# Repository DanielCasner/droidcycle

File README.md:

droidcycle
==========

Hardware and firmware for my Android phone based electric bicycle computer.

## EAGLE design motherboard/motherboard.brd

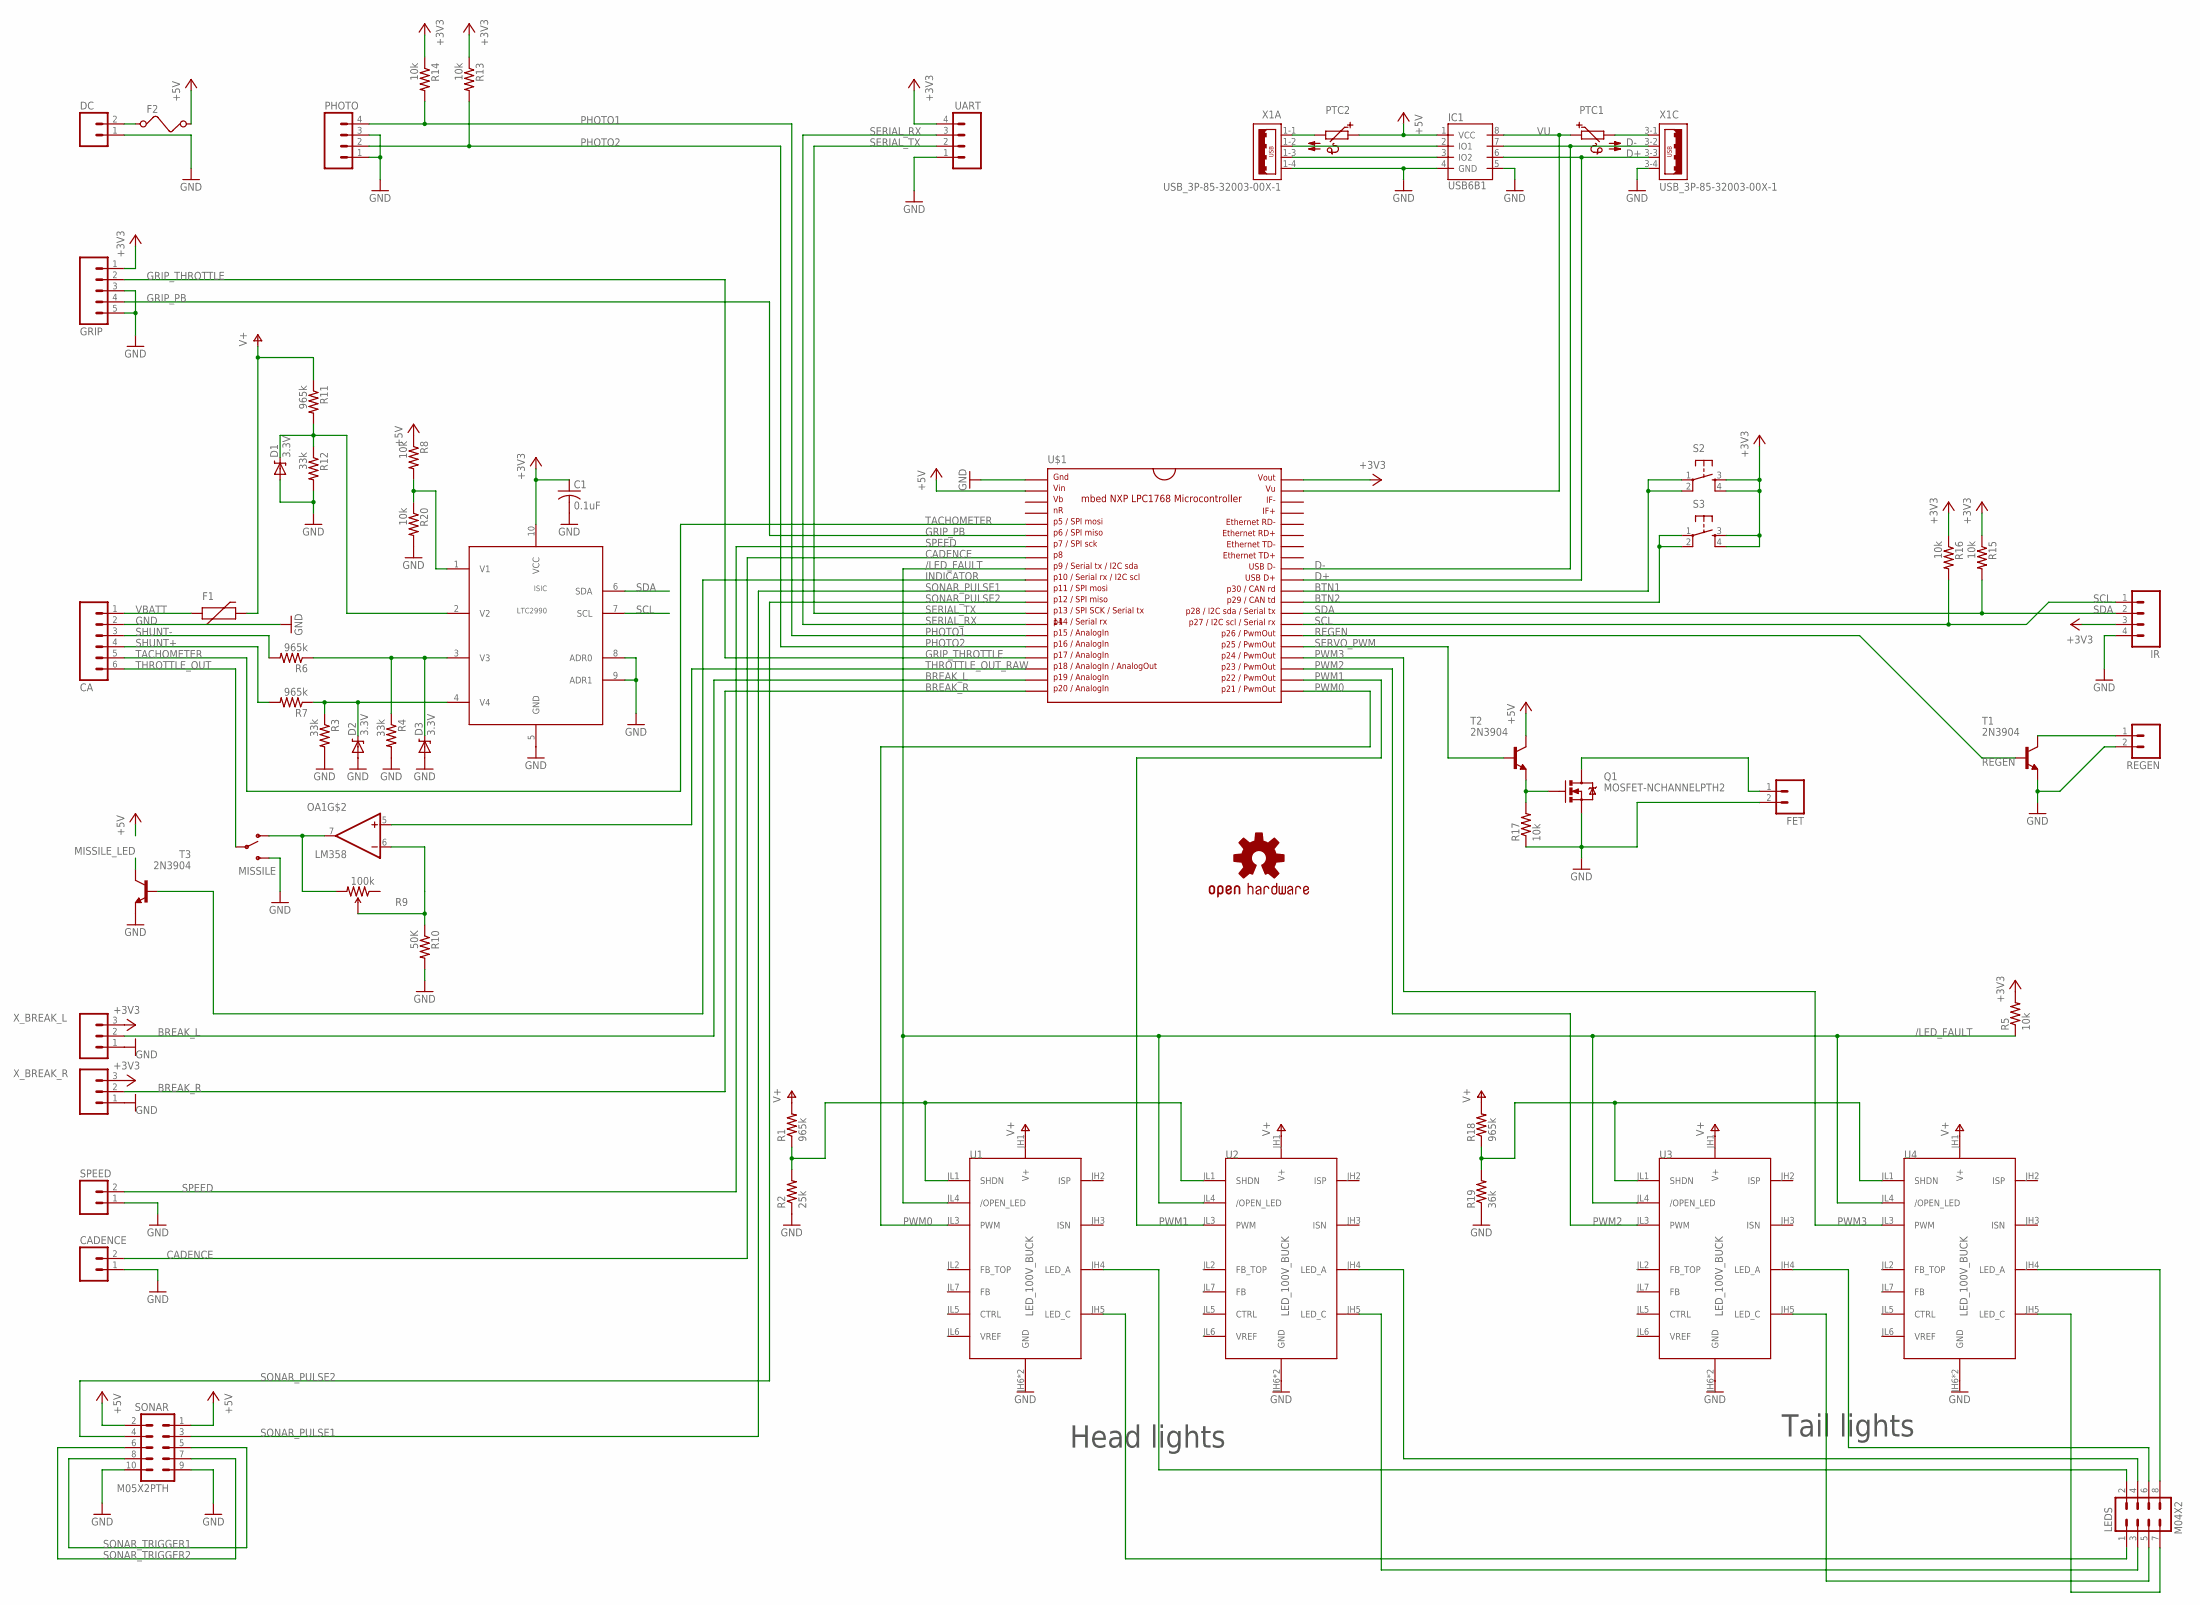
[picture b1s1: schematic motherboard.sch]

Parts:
C1: 0.1uF; C050-025X075
CA: M06; 06P
CADENCE: M02JST-PTH-2-KIT; JST-2-PTH-KIT
D1, D2, D3: 3.3V; DIODE-ZENER
DC: M02JST-PTH-2-KIT; JST-2-PTH-KIT
F1: PTCPTH; PTC
F2: FUSE
FET: M02JST-PTH-2-KIT; JST-2-PTH-KIT
GRIP: M05; 05P
IC1: USB6B1; SO08
IR: M04; 04P
ISIC: LTC2990; MSOP10
LEDS: M04X2; 2X4
MISSILE: SWITCH-SPDTPTH; SWITCH-SPDT
OA1: LM358; DIP08
PHOTO: M04JST-PTH; JST-4-PTH
PTC1, PTC2: PTC679; P679
Q1: MOSFET-NCHANNELPTH2; TO220V
R1, R6, R7, R11, R18: 965k; 0204/5
R2: 25k; 0204/5
R3, R4, R12: 33k; 0204/5
R5, R8, R13, R14, R15, R16, R17, R20: 10k; 0204/5
R9: 100k; 3362U-2
R10: 50K; 0204/5
R19: 36k; 0204/5
REGEN: M02JST-PTH-2-KIT; JST-2-PTH-KIT
S2, S3: TAC_SWITCHPTH; TACTILE-PTH
SONAR: M05X2PTH; AVR_ICSP
SPEED: M02JST-PTH-2-KIT; JST-2-PTH-KIT
T1, T2, T3: 2N3904; TO92
U1, U2, U3, U4: LED_100V_BUCK
U$1: MBED_NXP_LPC1768; DIL40_0.9
U$2: OSHW-LOGOL; OSHW-LOGO-L
UART: M04JST-PTH; JST-4-PTH
X1: USB_3P-85-32003-00X-1; 85-32003-00X-1
X_BREAK_L: M03JST-PTH; JST-3-PTH
X_BREAK_R: M03JST-PTH; JST-3-PTH

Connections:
+3V3: C1.1, GRIP.1, IR.3, ISIC.10 (VCC), R5.2, R13.1, R14.1, R15.1, R16.1, S2.3, S2.4, S3.3, S3.4, U$1.40, UART.4, X_BREAK_L.3, X_BREAK_R.3
+5V: F2.2, IC1.1 (VCC), PTC2.1, R8.1, SONAR.1, SONAR.2, T2.1 (C), U$1.2
/LED_FAULT: R5.1, U1.JL4 (/OPEN_LED), U2.JL4 (/OPEN_LED), U3.JL4 (/OPEN_LED), U4.JL4 (/OPEN_LED), U$1.9
BATT_SENSE: D1.P$1 (C), ISIC.2 (V2), R11.2, R12.1
BREAK_L: U$1.19, X_BREAK_L.2
BREAK_R: U$1.20, X_BREAK_R.2
BTN1: S2.1, S2.2, U$1.30
BTN2: S3.1, S3.2, U$1.29
CADENCE: CADENCE.2, U$1.8
D+: IC1.6 (IO2), U$1.31, X1.3-3 (3)
D-: IC1.7 (IO1), U$1.32, X1.3-2 (2)
GND: C1.2, CA.2, CADENCE.1, D1.P$2 (A), D2.P$2 (A), D3.P$2 (A), DC.1, FET.2, GRIP.3, GRIP.5, IC1.4 (GND), IC1.5 (GND), IR.4, ISIC.5 (GND), ISIC.8 (ADR0), ISIC.9 (ADR1), MISSILE.3 (S), PHOTO.1, PHOTO.3, Q1.3 (S), R2.1, R3.2, R4.2, R10.2, R12.2, R17.1, R19.1, R20.2, REGEN.2, SONAR.9, SONAR.10, SPEED.1, T1.3 (E), T3.3 (E), U1.JH6 (GND), U1.JL8 (GND), U2.JH6 (GND), U2.JL8 (GND), U3.JH6 (GND), U3.JL8 (GND), U4.JH6 (GND), U4.JL8 (GND), U$1.1, UART.1, X1.1-4 (4), X1.3-4 (4), X_BREAK_L.1, X_BREAK_R.1
GRIP_PB: GRIP.4
GRIP_THROTTLE: GRIP.2, U$1.17
INDICATOR: T3.2 (B), U$1.10
MISSILE_LED: T3.1 (C)
unnamed: PTC1.2, X1.3-1 (1)
unnamed: LEDS.1, U1.JH5 (LED_C)
unnamed: LEDS.3, U2.JH5 (LED_C)
unnamed: LEDS.5, U3.JH5 (LED_C)
unnamed: LEDS.7, U4.JH5 (LED_C)
unnamed: LEDS.2, U1.JH4 (LED_A)
unnamed: LEDS.4, U2.JH4 (LED_A)
unnamed: LEDS.6, U3.JH4 (LED_A)
unnamed: LEDS.8, U4.JH4 (LED_A)
unnamed: R1.1, R2.2, U1.JL1 (SHDN), U2.JL1 (SHDN)
unnamed: R18.1, R19.2, U3.JL1 (SHDN), U4.JL1 (SHDN)
unnamed: D3.P$1 (C), ISIC.3 (V3), R4.1, R6.1
unnamed: IC1.2 (IO1), X1.1-2 (2)
unnamed: Q1.1 (G), R17.2, T2.3 (E)
unnamed: PTC2.2, X1.1-1 (1)
unnamed: IC1.3 (IO2), X1.1-3 (3)
unnamed: D2.P$1 (C), ISIC.4 (V4), R3.1, R7.1
unnamed: R9.2 (WIPER), R10.1
unnamed: MISSILE.1 (O), OA1.7 (OUT), R9.3 (CW)
unnamed: ISIC.1 (V1), R8.2, R20.1
unnamed: DC.2, F2.1
unnamed: REGEN.1, T1.1 (C)
unnamed: FET.1, Q1.2 (D)
PHOTO1: PHOTO.4, R14.2, U$1.15
PHOTO2: PHOTO.2, R13.2, U$1.16
PWM0: U1.JL3 (PWM), U$1.21
PWM1: U2.JL3 (PWM), U$1.22
PWM2: U3.JL3 (PWM), U$1.23
PWM3: U4.JL3 (PWM), U$1.24
REGEN: T1.2 (B), U$1.26
SCL: IR.1, ISIC.7 (SCL), R16.2, U$1.27
SDA: IR.2, ISIC.6 (SDA), R15.2, U$1.28
SERIAL_RX: U$1.14, UART.3
SERIAL_TX: U$1.13, UART.2
SERVO_PWM: T2.2 (B), U$1.25
SHUNT+: CA.4, R7.2
SHUNT-: CA.3, R6.2
SONAR_PULSE1: SONAR.3, U$1.11
SONAR_PULSE2: SONAR.4, U$1.12
SONAR_TRIGGER1: SONAR.5, SONAR.8
SONAR_TRIGGER2: SONAR.6, SONAR.7
SPEED: SPEED.2, U$1.7
TACHOMETER: CA.5
THROTTLE_OUT: CA.6, MISSILE.2
THROTTLE_OUT_RAW: OA1.5 (+IN), U$1.18
V+: F1.P$2 (2), OA1.8 (V+), R1.2, R11.1, R18.2, U1.JH1 (V+), U2.JH1 (V+), U3.JH1 (V+), U4.JH1 (V+)
V-: OA1.4 (V-)
VBATT: CA.1, F1.P$1 (1)
VU: IC1.8 (VCC), PTC1.1, U$1.39

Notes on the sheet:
Head lights
Tail lights

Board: 2 copper layers, 59 parts (0 on the bottom side), 61 nets, no tracks yet.

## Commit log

2012-07-08 Add motherboard schematic.
2012-07-08 Getting started.
2012-07-09 incremental progress
2012-07-12 Added signals between led drivers and mcu, still need voltage feedback
2012-07-19 Complete schematic
    This commit uses generic part selections and has no board layout yet.
2012-08-11 Ready for parts and firmware
    Far enough along now to determine the size of the perfboard to put this
    on (6" x 6") and to start working on a BOM and firmware. My plan now is
    to get a little ways in to the firmware and place the order when I'm
    sure the firmware won't require hardware design changes.
2012-08-14 Added model of 10mm LED for lights
2012-08-17 Add beginnings of models of the breadboard and enclosure.
2012-08-17 Something like what the enclosure will look like.
    Enough of an assembly to start thinking about what it will look like.
2012-08-25 Add under voltage cutoff to LED drivers
    Add exports of the motherboard schematic.
2012-08-25 Increase resolution of motherboard image export
2012-08-28 Completely different approach to modeling the box.
2012-08-29 Continuing incremental progress on the enclosure design.
2012-08-31 Shrink the enclosure down and remove 4 LEDs to save cost.
    Update the assembly a little bit.
    Add an STL export of the enclosure bottom at current revision.
2012-09-04 Add mounting surface for the PCB
2012-09-05 Enough progress to make the assembly worth looking at.
2012-09-14 Added sonar module to the front
    Added some more fillets around the sensors.
    Adjusted the geometry and LED angles.
    Added test chamfer around 2 of the LEDs.
2012-09-19 Almost complete
    Bottom enclosure finished (I hope)
    Added model of usb receptical.
    Added enclosure top. Still needs switch hole.
    Updated assembly and rendering thereof.
2012-09-24 Added more holes
    Fastener holes for lid.
    Wiring holes in bottom.
    *** Found interference between lid and top row of LEDs so some
    adjustment will be required. ***
2012-09-25 Finish enclusure design.
    Unless I think of any more features it needs…
    Now to see where I can get it printed.
2012-09-25 Add exported STL files of enclosure parts.
2012-10-01 Add LTC2990 current and voltage monitoring chip
    Still needs to be connected.
2012-10-03 Finish adding voltage monitoring IC.
    Generate bill of materials.
2012-10-04 Update exported files
2012-10-04 Add driver for missile switch led and reexport files.
2012-10-08 Added missile switch to the model
    Missile switch will require cutting the corner out of the perf board.
    Still need a good solution for the USB connector to the smart phone.
2012-10-09 Add mounting features for sonar.
2012-10-11 Shrink long axis by .5cm to make it fit in 8"x8" printer workspace.
2012-10-12 Started working on rear light enclosure.
2012-10-12 Finish tail light enclosure and export STL.
2012-10-16 More accurate model of PCB and consequences
    Adjusted PCB mounting surface.
    Moved switch location slightly to avoid interference.
    Added cuttout to PCB.
2012-10-18 Final export of top before printing
2012-10-18 minmal change to assembly
2012-11-23 Fix wiring of LED fault signal and leble LED indicator signal.

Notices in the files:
parts and their libraries:
SparkFun-DigitalIC: Licensing: CC v3.0 Share-Alike You are welcome to use this library for commercial purposes.
